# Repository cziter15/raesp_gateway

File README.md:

# Project: RaESP Gateway
[![Build with PlatformIO](https://img.shields.io/badge/build%20with-PlatformIO-orange?logo=data%3Aimage%2Fsvg%2Bxml%3Bbase64%2CPHN2ZyB3aWR0aD0iMjUwMCIgaGVpZ2h0PSIyNTAwIiB2aWV3Qm94PSIwIDAgMjU2IDI1NiIgeG1sbnM9Imh0dHA6Ly93d3cudzMub3JnLzIwMDAvc3ZnIiBwcmVzZXJ2ZUFzcGVjdFJhdGlvPSJ4TWlkWU1pZCI+PHBhdGggZD0iTTEyOCAwQzkzLjgxIDAgNjEuNjY2IDEzLjMxNCAzNy40OSAzNy40OSAxMy4zMTQgNjEuNjY2IDAgOTMuODEgMCAxMjhjMCAzNC4xOSAxMy4zMTQgNjYuMzM0IDM3LjQ5IDkwLjUxQzYxLjY2NiAyNDIuNjg2IDkzLjgxIDI1NiAxMjggMjU2YzM0LjE5IDAgNjYuMzM0LTEzLjMxNCA5MC41MS0zNy40OUMyNDIuNjg2IDE5NC4zMzQgMjU2IDE2Mi4xOSAyNTYgMTI4YzAtMzQuMTktMTMuMzE0LTY2LjMzNC0zNy40OS05MC41MUMxOTQuMzM0IDEzLjMxNCAxNjIuMTkgMCAxMjggMCIgZmlsbD0iI0ZGN0YwMCIvPjxwYXRoIGQ9Ik0yNDkuMzg2IDEyOGMwIDY3LjA0LTU0LjM0NyAxMjEuMzg2LTEyMS4zODYgMTIxLjM4NkM2MC45NiAyNDkuMzg2IDYuNjEzIDE5NS4wNCA2LjYxMyAxMjggNi42MTMgNjAuOTYgNjAuOTYgNi42MTQgMTI4IDYuNjE0YzY3LjA0IDAgMTIxLjM4NiA1NC4zNDYgMTIxLjM4NiAxMjEuMzg2IiBmaWxsPSIjRkZGIi8+PHBhdGggZD0iTTE2MC44NjkgNzQuMDYybDUuMTQ1LTE4LjUzN2M1LjI2NC0uNDcgOS4zOTItNC44ODYgOS4zOTItMTAuMjczIDAtNS43LTQuNjItMTAuMzItMTAuMzItMTAuMzJzLTEwLjMyIDQuNjItMTAuMzIgMTAuMzJjMCAzLjc1NSAyLjAxMyA3LjAzIDUuMDEgOC44MzdsLTUuMDUgMTguMTk1Yy0xNC40MzctMy42Ny0yNi42MjUtMy4zOS0yNi42MjUtMy4zOWwtMi4yNTggMS4wMXYxNDAuODcybDIuMjU4Ljc1M2MxMy42MTQgMCA3My4xNzctNDEuMTMzIDczLjMyMy04NS4yNyAwLTMxLjYyNC0yMS4wMjMtNDUuODI1LTQwLjU1NS01Mi4xOTd6TTE0Ni41MyAxNjQuOGMtMTEuNjE3LTE4LjU1Ny02LjcwNi02MS43NTEgMjMuNjQzLTY3LjkyNSA4LjMyLTEuMzMzIDE4LjUwOSA0LjEzNCAyMS41MSAxNi4yNzkgNy41ODIgMjUuNzY2LTM3LjAxNSA2MS44NDUtNDUuMTUzIDUxLjY0NnptMTguMjE2LTM5Ljc1MmE5LjM5OSA5LjM5OSAwIDAgMC05LjM5OSA5LjM5OSA5LjM5OSA5LjM5OSAwIDAgMCA5LjQgOS4zOTkgOS4zOTkgOS4zOTkgMCAwIDAgOS4zOTgtOS40IDkuMzk5IDkuMzk5IDAgMCAwLTkuMzk5LTkuMzk4em0yLjgxIDguNjcyYTIuMzc0IDIuMzc0IDAgMSAxIDAtNC43NDkgMi4zNzQgMi4zNzQgMCAwIDEgMCA0Ljc0OXoiIGZpbGw9IiNFNTcyMDAiLz48cGF0aCBkPSJNMTAxLjM3MSA3Mi43MDlsLTUuMDIzLTE4LjkwMWMyLjg3NC0xLjgzMiA0Ljc4Ni01LjA0IDQuNzg2LTguNzAxIDAtNS43LTQuNjItMTAuMzItMTAuMzItMTAuMzItNS42OTkgMC0xMC4zMTkgNC42Mi0xMC4zMTkgMTAuMzIgMCA1LjY4MiA0LjU5MiAxMC4yODkgMTAuMjY3IDEwLjMxN0w5NS44IDc0LjM3OGMtMTkuNjA5IDYuNTEtNDAuODg1IDIwLjc0Mi00MC44ODUgNTEuODguNDM2IDQ1LjAxIDU5LjU3MiA4NS4yNjcgNzMuMTg2IDg1LjI2N1Y2OC44OTJzLTEyLjI1Mi0uMDYyLTI2LjcyOSAzLjgxN3ptMTAuMzk1IDkyLjA5Yy04LjEzOCAxMC4yLTUyLjczNS0yNS44OC00NS4xNTQtNTEuNjQ1IDMuMDAyLTEyLjE0NSAxMy4xOS0xNy42MTIgMjEuNTExLTE2LjI4IDMwLjM1IDYuMTc1IDM1LjI2IDQ5LjM2OSAyMy42NDMgNjcuOTI2em0tMTguODItMzkuNDZhOS4zOTkgOS4zOTkgMCAwIDAtOS4zOTkgOS4zOTggOS4zOTkgOS4zOTkgMCAwIDAgOS40IDkuNCA5LjM5OSA5LjM5OSAwIDAgMCA5LjM5OC05LjQgOS4zOTkgOS4zOTkgMCAwIDAtOS4zOTktOS4zOTl6bS0yLjgxIDguNjcxYTIuMzc0IDIuMzc0IDAgMSAxIDAtNC43NDggMi4zNzQgMi4zNzQgMCAwIDEgMCA0Ljc0OHoiIGZpbGw9IiNGRjdGMDAiLz48L3N2Zz4=)](https://platformio.org/)

**Ra-02 (SX1278) + ESP12-S (ESP8266) gateway**

## What and why?
A few years ago (2018), when I began designing electronics for fun, I made something like a WiFi-controlled 433 MHz remote for RC power outlets I bought from the store. The first version was a mess because I had no clue how to design a PCB. I just connected all the 'wires' on a two-layer board and flooded everything with ground. It worked, but not as reliably as I hoped. Later, I redesigned the board with a focus on minimizing current loops, but even then, not everything worked as intended. More info [here](https://hackaday.io/project/163833-wifi-to-433-mhz-bridge).

In the end, I decided to switch to the Ra-02 instead of the RFM110W. It's theoretically a much better choice because it's programmable and not just a transmitter, but also a transceiver. This means I can both send and receive messages, without being limited to OOK. It even supports LoRa, FSK, and more!

## Hardware overview

To build my PCB, I kept the component count minimal—just a few capacitors, resistors, an LDO regulator (AMS1117) to step down 5V from USB to 3.3V for the modules, an ESP12-S (ESP8266-based module) as the application brain for WiFi connectivity, and a RA-02 (SX1278-based module) to handle all the RF work.

## Software overview

The software is C++ based and powered by [ksIotFrameworkLib](https://github.com/cziter15/ksIotFrameworkLib). It currently supports MQTT and implements the following protocols:

- Ningbo RF protocol
- Nexa RF protocol

At the moment, it only works in transmitter mode, but it's also possible to implement LoRa functionality in the future.

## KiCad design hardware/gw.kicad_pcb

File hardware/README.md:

# Hardware design : raesp_gateway

## Schematic

## Renders

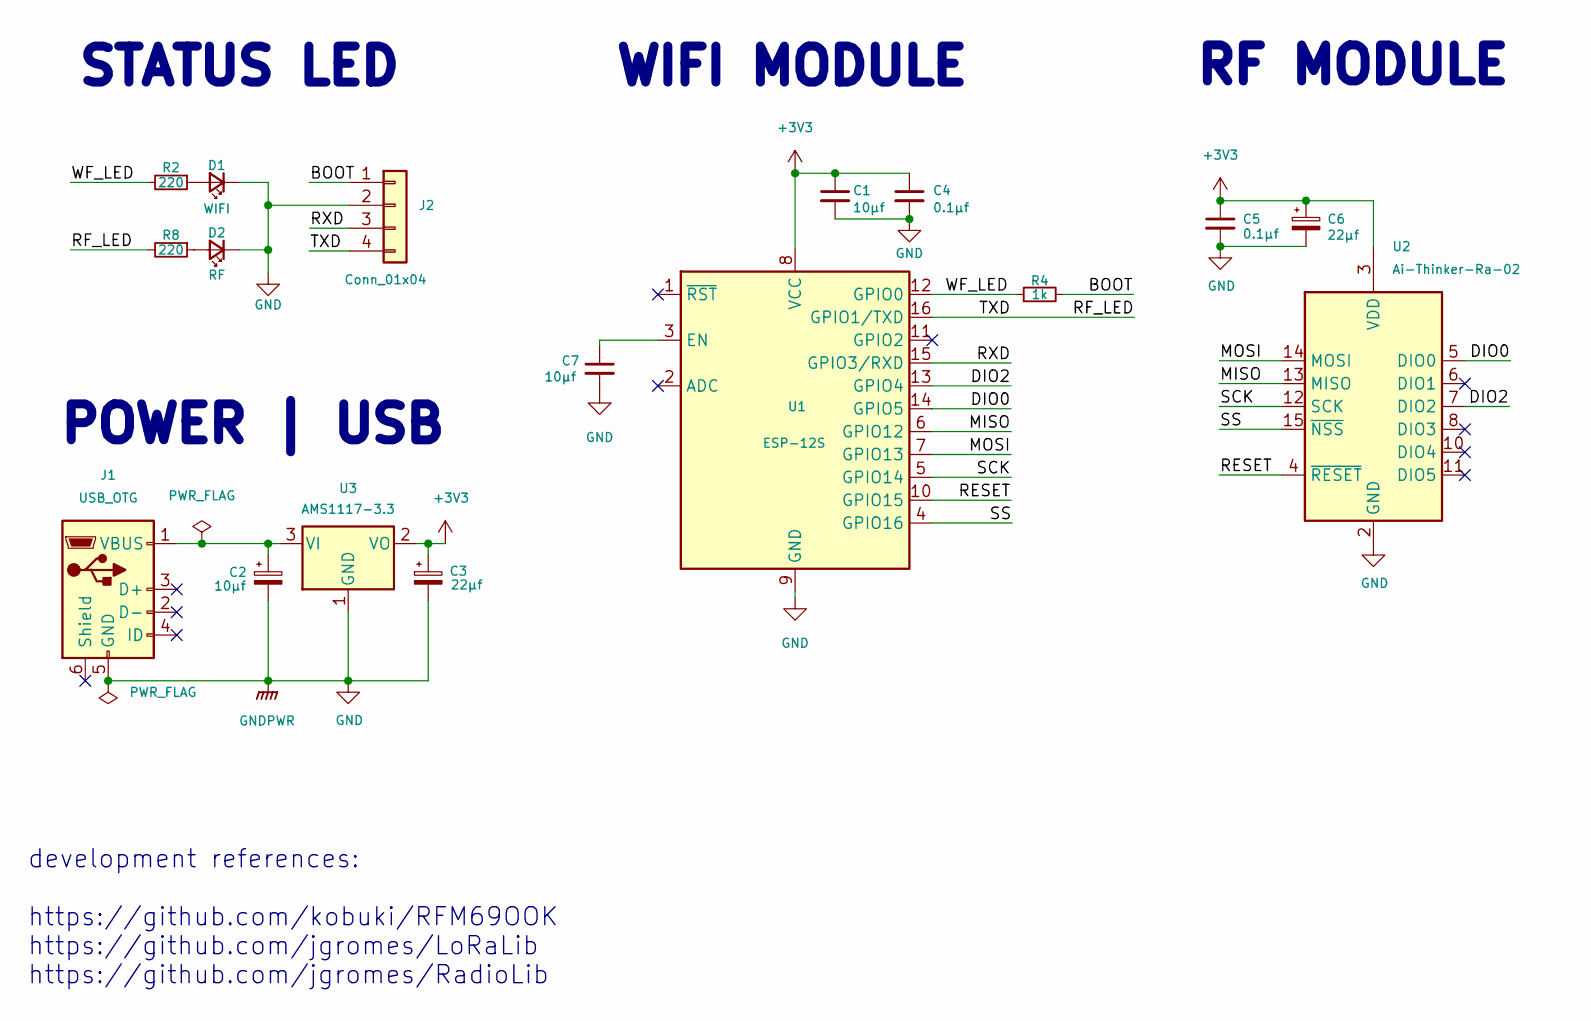
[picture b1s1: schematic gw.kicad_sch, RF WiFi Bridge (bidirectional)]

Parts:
C1, C7: 10µf; C_1206_3216Metric; LCSC C126946
C2: 10µf; CP_EIA-3216-10_Kemet-I; LCSC C126946
C3, C6: 22µf; CP_EIA-3216-10_Kemet-I; LCSC C126946
C4, C5: 0.1µf; C_1206_3216Metric
D1: WIFI; LED_1206_3216Metric; LCSC C375459
D2: RF; LED_1206_3216Metric; LCSC C375459
J1: USB_OTG; USB_Micro-B_Molex-105017-0001
J2: Conn_01x04; PinHeader_1x04_P2.54mm_Vertical
R2, R8: 220; R_1206_3216Metric; LCSC C17948
R4: 1k; R_1206_3216Metric; LCSC C1489
U1: ESP-12S; ESP-07
U2: Ai-Thinker-Ra-02; Ai-Thinker-Ra-01-LoRa
U3: AMS1117-3.3; SOT-223-3_TabPin2; LCSC C6186

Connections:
+3V3: C1.1, C3.1, C4.1, C5.1, C6.1, U1.8 (VCC), U2.3 (VDD), U3.2 (VO)
/BOOT: J2.1, R4.2
/DIO0: U1.14 (GPIO5), U2.5 (DIO0)
/DIO2: U1.13 (GPIO4), U2.7 (DIO2)
/MISO: U1.6 (GPIO12), U2.13 (MISO)
/MOSI: U1.7 (GPIO13), U2.14 (MOSI)
/RESET: U1.10 (GPIO15), U2.4 (~RESET)
/RF_LED: J2.4, R8.2, U1.16 (GPIO1/TXD)
/RXD: J2.3, U1.15 (GPIO3/RXD)
/SCK: U1.5 (GPIO14), U2.12 (SCK)
/SS: U1.4 (GPIO16), U2.15 (~NSS)
/WF_LED: R2.2, R4.1, U1.12 (GPIO0)
GND: C1.2, C2.2, C3.2, C4.2, C5.2, C6.2, C7.2, D1.1 (K), D2.1 (K), J1.5 (GND), J2.2, U1.9 (GND), U2.1 (GND), U2.2 (GND), U2.9 (GND), U2.16 (GND), U3.1 (GND)
unnamed: C2.1, J1.1 (VBUS), U3.3 (VI)
unnamed: C7.1, U1.3 (EN)
unnamed: D1.2 (A), R2.1
unnamed: D2.2 (A), R8.1

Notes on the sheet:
RF MODULE
development references: https://github.com/kobuki/RFM69OOK https://github.com/jgromes/LoRaLib https://github.com/jgromes/RadioLib
STATUS LED
WIFI MODULE
POWER | USB

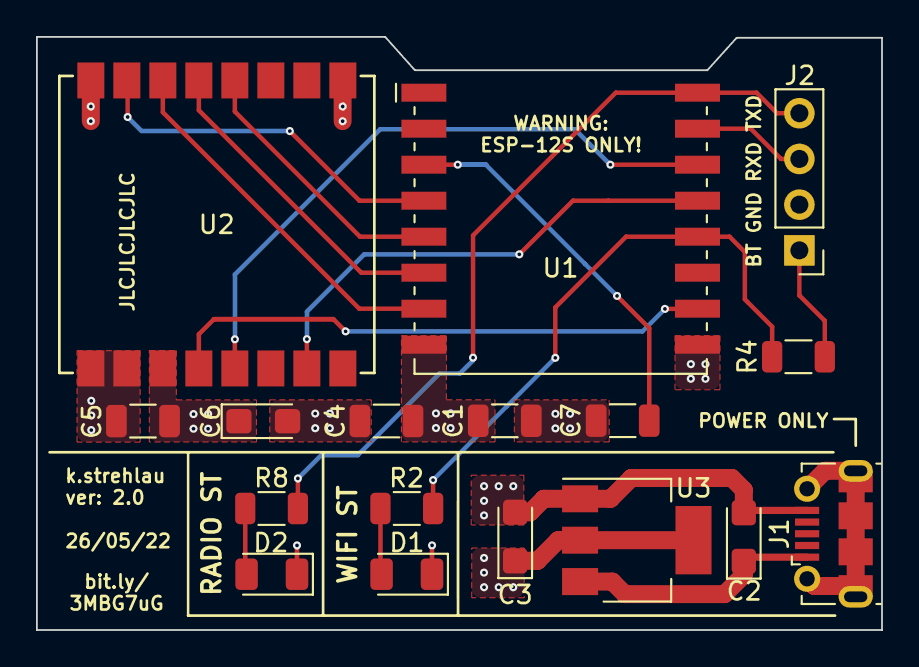
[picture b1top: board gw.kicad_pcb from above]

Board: 4 copper layers, 47.0 x 32.9 mm, 17 parts (0 on the bottom side), 17 nets.

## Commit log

2022-04-27 Change placement of PU resistors
2022-04-27 Add leds, fix layout
2022-04-27 Update schematics, almost fab ready
2022-04-27 Add DIO1 pin support
2022-04-27 Fix connector
2022-04-27 Fix errors
2022-04-27 Fix hole sizes
2022-04-27 Latest fixes
2022-04-27 Fixup pins
2022-04-28 Cleanup sch
2022-04-28 Latest prefab
2022-04-28 Name changes
2022-04-28 Fix rev
2022-04-28 Fix desc
2022-05-19 Change resistor value
2022-05-24 Initial commit for firmware
2022-05-25 Fixes
2022-05-25 Revert "Fixes", move to ESP12F
    This reverts commit ad443d04f57b2ab128a4687db847c72f3a41be2c.
2022-05-26 Revert "Revert "Fixes", move to ESP12F", sticking to ESP12S now.
    This reverts commit af2652227ade2a41ecb2737fc58930674a5f1724.
2022-05-26 Correct version in schematic
2022-05-28 Small fixes
2022-05-30 Add RFMacros.h
2022-06-06 Move to platformio
2022-06-06 Fix platformio.ini
2022-06-07 Changes to match new ksIotFrameworkLib version
2022-06-10 Fix OTA setup
2022-06-10 Use mdns instead of IP for OTA
2022-06-13 Update code to new hardware version
2022-06-14 Refactor radio module handler
2022-06-14 Remove unncessary txPin
2022-06-14 Unify msg
2022-06-14 Remove tail wait at protocols/nexa.cpp
2022-06-14 Small tweak nexa.cpp
2022-06-14 Fix repeats to be proper as earlier.
2022-06-14 Code cleanup
2022-06-14 Remove warning
2022-06-14 Fix wifi / radio led conflict
2022-06-14 Rename methods for tx
2022-06-14 No need to hold radioled ptr in device
2022-06-14 Update board image
2022-06-14 Update firmware readme
2022-06-15 RadioCommand file rename to RadioCommander
2022-06-16 Remove unnecessary flag
2022-06-16 Fix typo in platformio.ini
2022-06-17 Radio commander comments
2022-06-19 Remove nortti unflag, not required anymore as lib handles that
2022-07-06 Add pio badge
2022-07-06 Fix hyperlinks for badges
2022-07-08 Add subtopic for rfswitch
2022-07-08 Cleanup RadioCommander
2022-07-08 Add uptime badge
2022-07-09 Bump output power to 15 dBm
2022-07-10 Set 12 dBm power to PA
2022-07-11 Switch to NonOS SDK v2.2.x 191122
2022-07-14 Remove global ArduinoOTA
2022-07-29 Update project desc
2022-08-02 Remove interrupt disabling
2022-08-02 Get back to default ArduinoESP SDK
2022-08-09 Typo fix
2022-08-13 Fix build error
2022-08-15 Update to match new naming convention
2022-08-15 Fix initialization
2022-08-23 Update code to use new lib
2022-08-25 Update to new custom RTTI in new library
2022-08-29 Use std::from_chars
2022-09-04 Update to use ksf::from_chars
2022-09-04 Remove charconv, use ksf wrapper at to_string
2022-09-11 Lower TX power
2022-09-26 Change to build once per week
2022-09-30 Fix hostname
2022-10-18 Get back to .local domain
2022-10-23 Unify initialization
2022-10-27 Fix warning for CICD workflow
2022-10-27 Fix workflow to get rid of python version warning
2022-10-30 Fix namespace structure
2022-10-30 Bump TP to 13dBm
2022-11-01 Add temp sensor support
2022-11-01 Change TEMP_UPDATE_INTERVAL to 5 minutes
2022-11-01 Cleanup TempSensor code
2022-11-01 Add resolution selection, speedup conversio
2022-11-01 Increase temp res to 11 bit
2022-11-02 Extract temp resolution to constructor of TempSensor component.
2022-11-02 Skip sending invalid temp.
2022-11-02 Fix bug with TempSensor
2022-11-03 Change reporting value resolution
2022-11-04 Set 3 minute interval
2022-11-04 Send temp every 5 min instead of 3
2022-11-12 Small code cleanup
2022-11-13 Tweak temp sensor
2022-11-14 Update copyright headers, tweak variable names
2022-11-14 Fix a typo causing compiler error
2022-11-15 Comments for functions
2022-11-15 Change RAM preferences
2022-11-19 Fix project to work with latest ksIotFramework name changes.
2022-12-03 Comments, cleanup
2022-12-03 Change pin name
2022-12-07 Fix bug in ningbo protocol implementation
2022-12-08 Tweak onMqttMessage method
2022-12-08 Fix temp sensor
2022-12-08 Add OTA update indicator
2022-12-11 OTA as component
2022-12-11 Force standby when OTA flash starts.
2022-12-11 Remove redundant pointer
2022-12-12 AI assisted tweaks
2022-12-14 Fix tab
2022-12-19 Fix gateway code to be in sync with ksIotFrameworkLib
2022-12-22 Optimize Raesp firmware to use move semantics
2022-12-24 Fix ota init
2023-01-03 Add frequency hoping
2023-01-03 Correct power, add TX drive via PULLUP
2023-01-04 Make some cleanup
2023-01-04 use strength register
2023-01-04 try fix
2023-01-05 Get rid of drive strength things, it didnt help
2023-01-14 Use sdk 305
2023-01-24 Use app rotator
2023-01-25 Fix npos
2023-01-26 Use pio platform instead of git latest for esp
2023-01-26 Change speeds, cleanup platformio.ini
2023-04-07 Fix postinit
2023-04-08 Fix mqtt delegates
2023-04-08 Fix postinit method
2023-04-10 Add devstat reporter
2023-04-13 Fix sensor name
2023-07-08 Fix compilation warnings
2023-07-08 Fix comments
2023-07-08 Fix led pin
2023-08-25 Small optimizations
2023-09-17 Add elegantota
2023-09-18 Fix defs
2023-09-18 Fix bug
2023-09-18 Change defs
2023-09-22 Add device portal
2023-09-25 Fix typo in ini
2023-09-25 Fix non transmitting error
2023-09-25 Revert LED
2023-10-01 Use unique ptr for events
2023-10-01 Use higher bw LWIP
2023-10-01 Fix ini file
2023-10-02 Remove PGM macro
2023-10-06 Fix flags
2023-10-08 Refactor - remove ksSafeList
2023-10-08 Better passing for components
2023-10-10 Remove debug mqtt
2023-10-10 Enable app logs
2023-10-10 Fixes to get rid of mqtt log topic
2023-12-17 Multipower
2023-12-17 Auto-adjust power
2023-12-18 Revert latest changes
2023-12-20 Correct timings
2024-01-19 Use asm precision delay
2024-01-19 fix indent
2024-01-21 Fix timing
2024-01-23 set 10dbm
2024-01-24 Add proper value for radio shouting
2024-02-27 Revert ostick
2024-06-25 Fix build flags
2024-06-27 Cleanup pio ini
2024-06-27 Bugfix ini file
2024-06-27 Bugfix
2025-10-09 Initial plan
2025-10-09 Add comprehensive validation for DS18B20 temperature sensor readings
2025-10-09 Fix DS18B20 sensor communication timing issues
2025-10-09 Adjust parasitic power delay: 50ms every measurement
2025-10-09 Reset DS18B20 handler on invalid readings to recover from pin conflicts
2025-10-09 Always disable sensor power after measurement regardless of LED state
2025-10-09 Refactor: skip measurement if LED is on, use only register operations
2025-10-09 Fix TempSensor LED conflict by skipping measurement when LEDs are active
2025-10-09 Use named constant for parasitic capacitor charge delay
2025-10-09 Check pin values directly instead of LED blinking state
2025-10-09 Optimize TempSensor: skip measurement if MQTT disconnected or LED pin is HIGH, use GPIO registers
2025-10-09 Track MQTT connection state to skip measurements when disconnected
2025-10-09 Add thread safety and pin direction check for robustness
2025-10-09 Fix GPIO output detection to use GPOE register instead of GPC
2025-10-09 Use ksMqttConnector::isConnected() instead of manual state tracking
2025-10-09 Move MQTT connection check to loop() for better efficiency
2025-10-09 Refactor GPIO handling in TempSensor.cpp
2025-10-09 Refactor GPIO handling for temperature sensor
2025-10-12 Add [[maybe_unused]] attribute to unused function parameters
